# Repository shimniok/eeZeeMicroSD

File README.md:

eeZeeMicroSD is a microSD breakout board that is pin-aligned with ATmega328P so you can just plug it into the breadboard without jumpers

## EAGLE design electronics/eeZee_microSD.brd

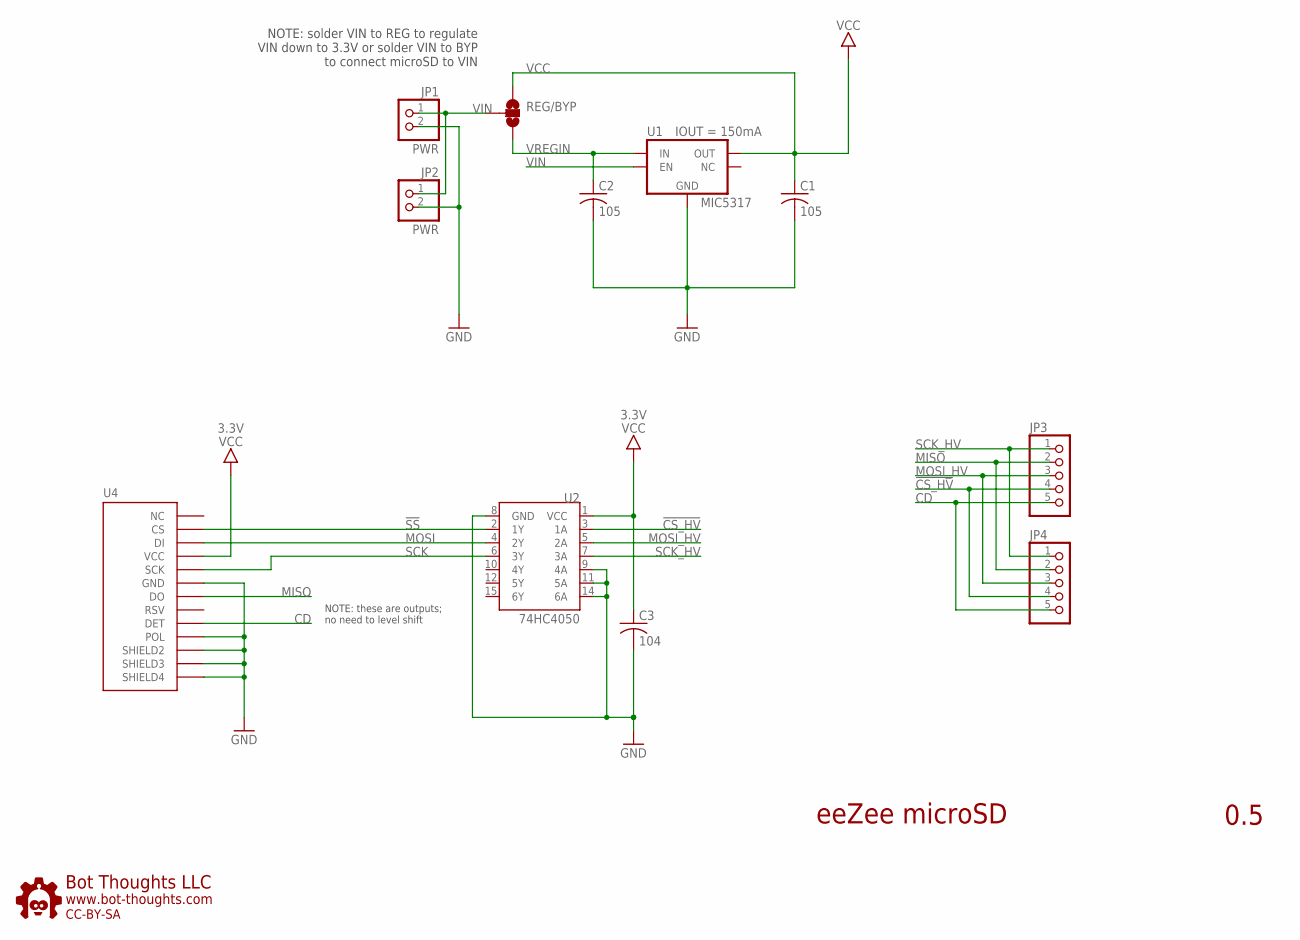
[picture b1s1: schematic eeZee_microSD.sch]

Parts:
C1, C2: 105; 0603; PARTNO LMK107B7105KA-T
C3: 104; C0603; PARTNO LMK107B7105KA-T
JP1, JP2: PWR; 1X02-S
JP3, JP4: PINHD-1X05_2.54-S; 1X05-S
REG/BYP: SOLDERJUMPER_2WAYS; SJ_3
U1: MIC5317; SOT23-5; PARTNO MIC5317-3.3YM5-TR
U2: 74HC4050; SO016
U4: MICROSD_CD; USD_SMALL
U$5: BTLOGO-LOGO-SM; BTLOGOS

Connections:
!CS_HV: JP3.4, JP4.4, U2.3 (1A)
!SS: U2.2 (1Y), U4.2 (CS)
CD: JP3.5, JP4.5, U4.DET
GND: C1.2 (-), C2.2 (-), C3.2, JP1.2, JP2.2, U1.2 (GND), U2.8 (GND), U2.9 (4A), U2.11 (5A), U2.14 (6A), U4.6 (GND), U4.GND1 (SHIELD2), U4.GND3 (SHIELD3), U4.GND4 (SHIELD4), U4.POL
MISO: JP3.2, JP4.2, U4.7 (DO)
MOSI: U2.4 (2Y), U4.3 (DI)
MOSI_HV: JP3.3, JP4.3, U2.5 (2A)
SCK: U2.6 (3Y), U4.5 (SCK)
SCK_HV: JP3.1, JP4.1, U2.7 (3A)
VCC: C1.1 (+), C3.1, REG/BYP.1, U1.5 (OUT), U2.1 (VCC), U4.4 (VCC)
VIN: JP1.1, JP2.1, REG/BYP.2, U1.3 (EN)
VREGIN: C2.1 (+), REG/BYP.3, U1.1 (IN)

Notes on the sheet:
NOTE: solder VIN to REG to regulate VIN down to 3.3V or solder VIN to BYP to connect microSD to VIN
eeZee microSD
0.5
NOTE: these are outputs; no need to level shift

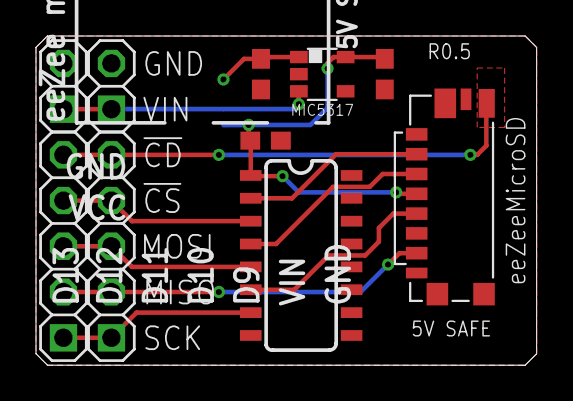
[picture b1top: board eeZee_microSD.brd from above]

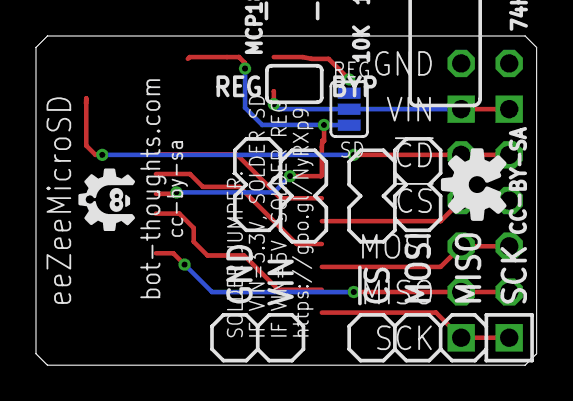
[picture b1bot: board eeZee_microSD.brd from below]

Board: 2 copper layers, 27.8 x 18.3 mm, 12 parts (2 on the bottom side), 12 nets.

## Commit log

2012-12-13 Initial revision
2012-12-13 Added name/rev
2012-12-30 Added offset power strip header, tweaked layout, optimized 74HC4050 pin use, etc.
2012-12-31 Minor tweaks/fixes.
2013-01-02 Rev 0.1 as ordered
2013-02-04 Layout tweaks to fix power pin alignment.
2013-06-14 Fixes to PropVGA, microSD,
2013-10-25 Renamed microSD files, moved to electronics subfolder
2013-10-25 Added Arduino example code / test
2014-04-15 Put testing in a loop for convenience.
2014-12-02 Modified prinout lines. Removed sd.end() because it (no longer?) exists.
2014-12-03 Change to initialize once after reset, repeats tests every 5 secs, shows pass/fail for each.
2015-04-24 Revised microSD test for use with new test jig
2015-04-24 Updated file header/comments, author, documentation.
2015-05-05 Added LICENSE files and README file.
2015-08-06 renamed microSD_Test1 to TestJig
2015-08-06 Renamed microSD_Test1.ino to TestJig.ino
2015-10-19 Switched to push-pull socket, shrank board, modified regulator and level shifter layouts, modified silk layout.
2015-10-19 modified silk layout
2015-10-19 Updated zip
2015-10-19 Updated schematic version and usd socket value
2015-10-26 Updated version with flip-top socket
2015-10-26 updated gerbers
2015-10-27 Used small manual connector. Total layout redesign, shrunk board considerably, removed power rail pin headers
2015-10-27 Additional layout changes, connected Card Detect
2015-11-02 Added user guide in Markdown
2015-12-03 Updated ReadWrite to initialize card only once
2015-12-03 Fixed silk error on reg/byp and moved solder jumper
2015-12-03 Changed solder jumper due to overheat of MCP1824.
2015-12-03 updated version #
2015-12-03 Fixed regulator overheat when BYP selected; removed jumper. Regulator outputs 3.3V when VIN=3.3V
2015-12-03 added gitignore
2015-12-03 board rerouting, layout, etc., to accommodate solder jumper that was removed
2015-12-03 updated power trace width
2015-12-03 updated gerbers, zip
2015-12-15 updated instructions for D9/cd pin, and updated errata for solder jumper
2021-10-14 new regulator
2022-03-08 rotated board
2022-03-08 convert to single component layer
2022-03-08 finished routing, silk, added instructions and help url
2022-03-08 fixed input/output caps per datasheet, changed DET to CD on silk
2022-03-08 moved solder jumper to bottom, tweaked silk, changed board layout.
2022-05-02 changed layout, silk, reg/byp, pwr routing, sd package (centered)
2022-05-02 revised byp/reg label, created gerbers, zip
2022-05-03 renamed tflash jpg file, added zip

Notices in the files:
electronics/eeZee_microSD.brd:
cc-by-sa
parts and their libraries:
SparkFun: Licensing: CC v3.0 Share-Alike You are welcome to use this library for commercial purposes.
